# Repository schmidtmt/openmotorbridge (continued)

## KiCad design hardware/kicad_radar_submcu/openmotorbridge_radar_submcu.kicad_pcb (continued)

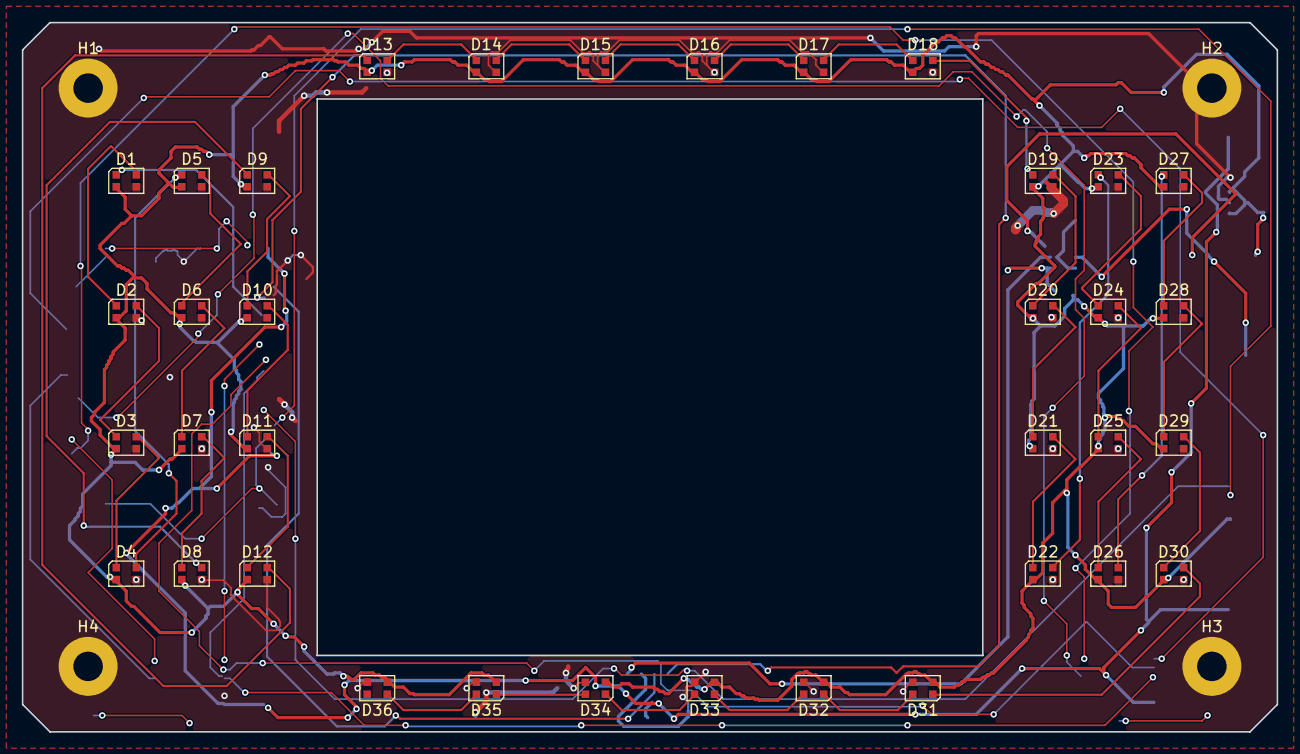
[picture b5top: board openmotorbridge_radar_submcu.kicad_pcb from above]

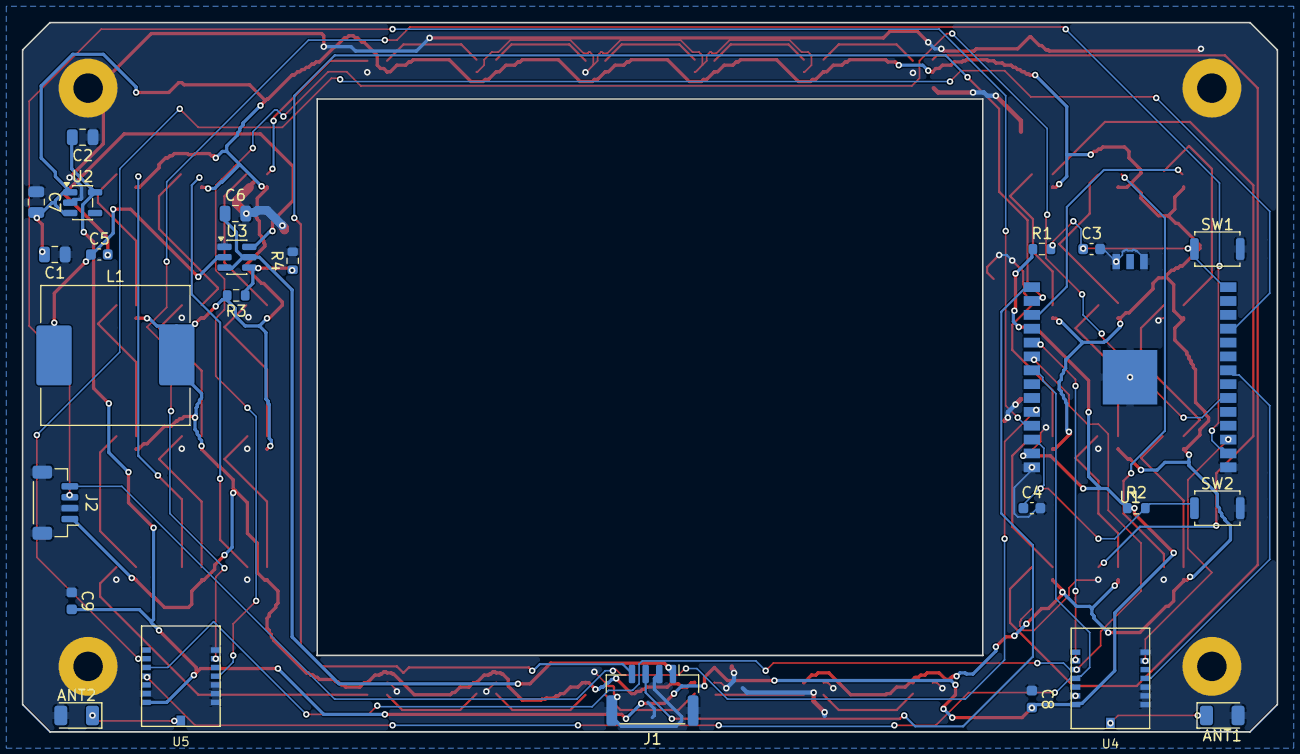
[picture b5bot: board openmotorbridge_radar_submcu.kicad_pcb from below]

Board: 2 copper layers, 115.0 x 65.0 mm, 65 parts (25 on the bottom side), 59 nets.

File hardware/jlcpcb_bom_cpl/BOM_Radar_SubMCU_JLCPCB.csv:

Designator,Comment,Footprint,LCSC Part #,Quantity
C1,10uF_16V,C_0805_2012Metric,,1
C2,10uF_10V,C_0805_2012Metric,,1
"C3, C4",100nF,C_0603_1608Metric,,2
D25,PESD5V0S2BT,SOT-23,,1
"D1, D10, D11, D12, D13, D14, D15, D16, D17, D18, D19, D2, D20, D21, D22, D23, D24, D25, D26, D27, D28, D29, D3, D30, D31, D32, D33, D34, D35, D36, D4, D5, D6, D7, D8, D9",WS2812B-2020,LED_WS2812B-2020_PLCC4_2.0x2.0mm,,36
"H1, H2, H3, H4",M2.5_MountingHole,MountingHole_2.7mm_M2.5_Pad,,4
J1,JST_SH_4P_CENTRAL,JST_SH_SM04B-SRSS-TB_1x04-1MP_P1.00mm_Horizontal,,1
J2,JST_SH_4P_MR20,JST_SH_SM04B-SRSS-TB_1x04-1MP_P1.00mm_Horizontal,,1
J3,U.FL_5G9_V2X,U.FL_Hirose_U.FL-R-SMT-1_Vertical,,1
"R1, R2",10k,R_0603_1608Metric,,2
SW1,BOOT_SW,SW_Push_SPST_NO_Alps_SKRK,,1
SW2,RESET_SW,SW_Push_SPST_NO_Alps_SKRK,,1
U1,ESP32-C5-WROOM-1U,ESP32-C3-WROOM-02U,,1
U2,TPS7A0533,SOT-23-5,,1

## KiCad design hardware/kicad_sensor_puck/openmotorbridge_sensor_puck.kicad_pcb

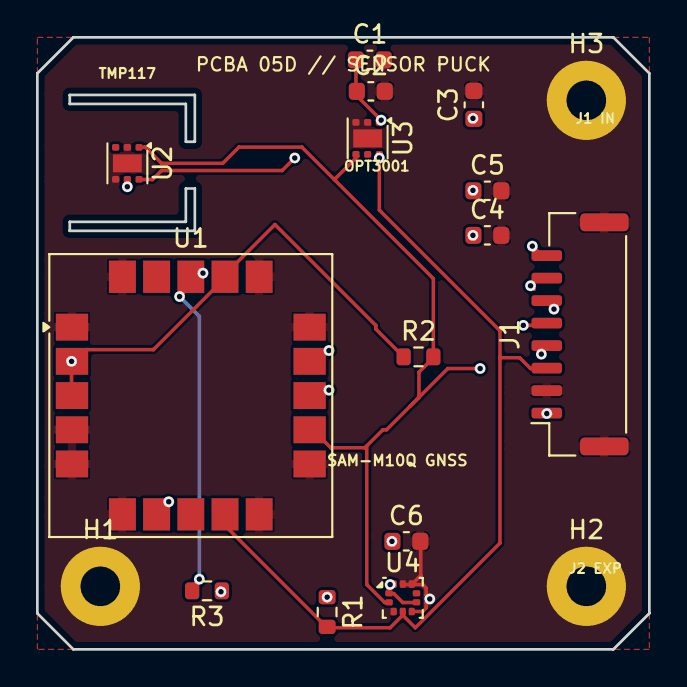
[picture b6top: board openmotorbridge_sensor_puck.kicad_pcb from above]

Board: 4 copper layers, 34.0 x 34.0 mm, 17 parts (0 on the bottom side), 8 nets.

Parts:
C1, C3, C4, C6: 0.1uF; C_0603_1608Metric
C2: 4.7uF; C_0603_1608Metric
C5: 10uF; C_0603_1608Metric
H1, H2, H3: M2; MountingHole_2.2mm_M2_Pad
J1: JST_GH_08P_SENSOR_IN; JST_GH_SM08B-GHS-TB_1x08-1MP_P1.25mm_Horizontal
R1, R2: 4.7k; R_0603_1608Metric
R3: 10k; R_0603_1608Metric
U1: SAM-M10Q; ublox_SAM-M8Q
U2: TMP117AIDRVR; WSON-6-1EP_2x2mm_P0.65mm_EP1x1.6mm
U3: OPT3001DNPR; WSON-6-1EP_2x2mm_P0.65mm_EP1x1.6mm
U4: BMP390; ST_HLGA-10_2x2mm_P0.5mm_LayoutBorder3x2y

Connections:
GND: C1.2, C2.2, C3.2, C4.2, C5.2, C6.2, H1.1 (1_1), H2.1 (1_1), H3.1 (1_1), J1.2, J1.MP, U1.1, U1.4, U1.5, U1.6, U1.10, U1.11, U1.15, U1.16, U1.20, U2.2, U2.4, U2.7, U3.2, U3.3, U3.7, U4.3, U4.5, U4.8, U4.9
GNSS_RESET_N: J1.8, R3.2, U1.18
GNSS_RXD: J1.7, U1.14
GNSS_TIMEPULSE: J1.5, U1.7
GNSS_TXD: J1.6, U1.13
I2C_SCL: J1.4, R2.2, U1.12, U2.1, U3.4, U4.2
I2C_SDA: J1.3, R1.2, U1.9, U2.6, U3.6, U4.4
VCC_3V3: C1.1, C2.1, C3.1, C4.1, C5.1, C6.1, J1.1, R1.1, R2.1, R3.1, U1.2, U1.3, U1.17, U2.5, U3.1, U4.1, U4.6, U4.10

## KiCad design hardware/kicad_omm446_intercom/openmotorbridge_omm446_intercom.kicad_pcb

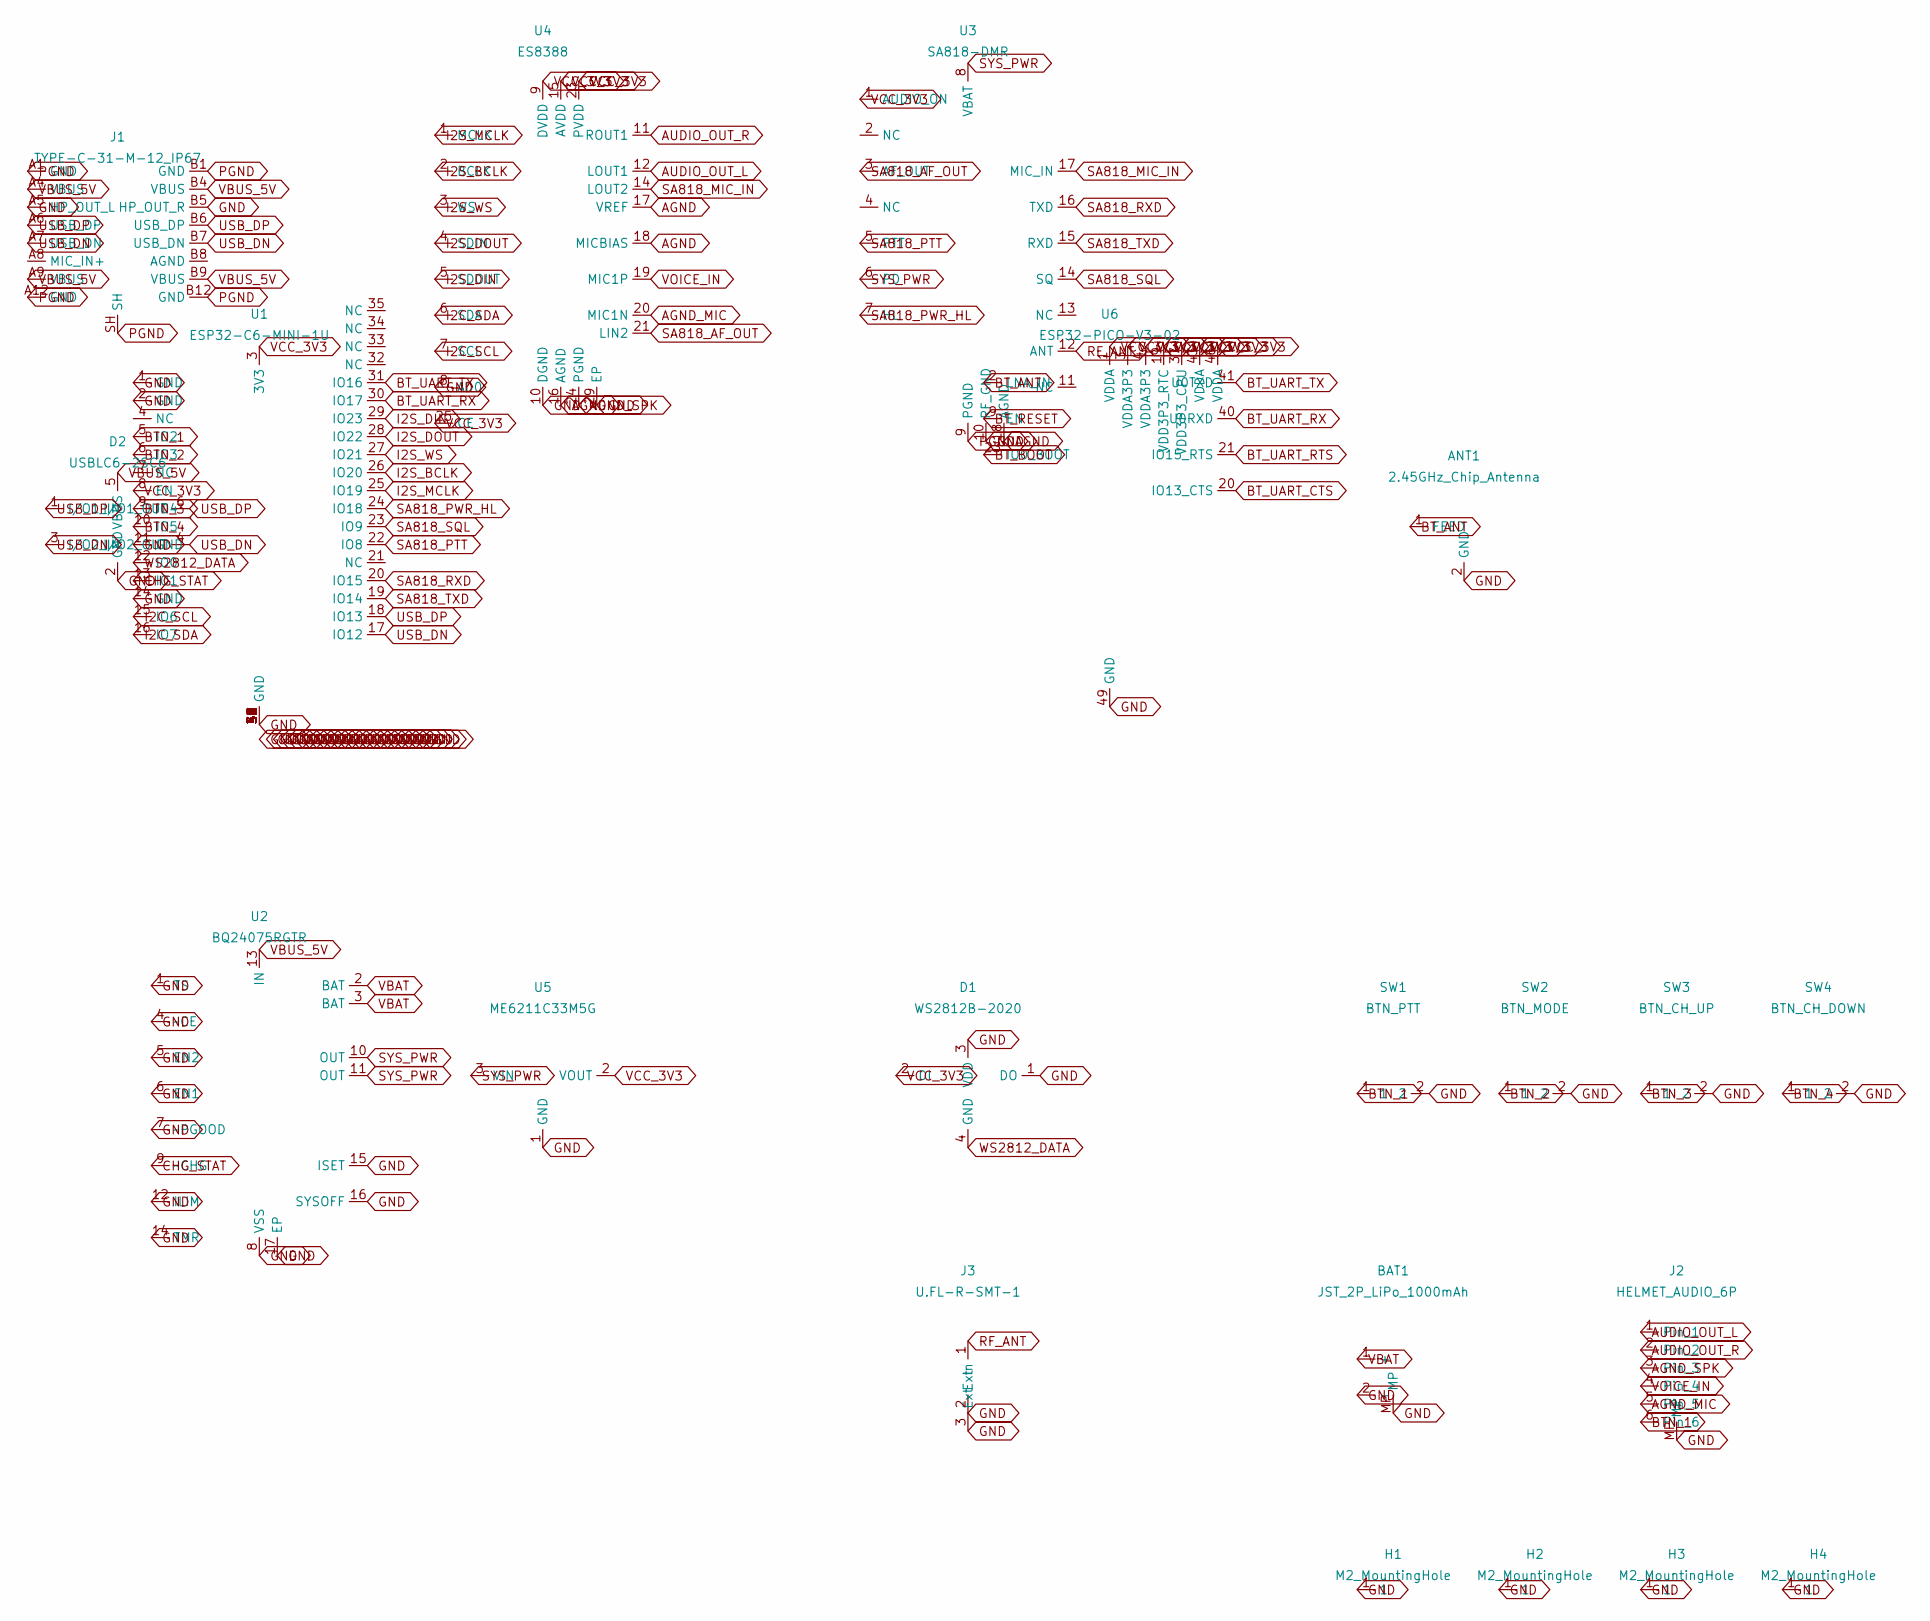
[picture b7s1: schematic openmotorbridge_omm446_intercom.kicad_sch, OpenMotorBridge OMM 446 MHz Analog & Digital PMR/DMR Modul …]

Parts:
ANT1: 2.45GHz_Chip_Antenna; Johanson_2450AT18x100; LCSC C2909988
BAT1: JST_2P_LiPo_1000mAh; JST_SH_BM02B-SRSS-TB_1x02-1MP_P1.00mm_Vertical
D1: WS2812B-2020; LED_WS2812B-2020_PLCC4_2.0x2.0mm
D2: USBLC6-2SC6; SOT-23-6
H1, H2, H3, H4: M2_MountingHole; MountingHole_2.2mm_M2_Pad
J1: TYPE-C-31-M-12_IP67; USB_C_Receptacle_HRO_TYPE-C-31-M-12
J2: HELMET_AUDIO_6P; JST_SH_BM06B-SRSS-TB_1x06-1MP_P1.00mm_Vertical
J3: U.FL-R-SMT-1; U.FL_Hirose_U.FL-R-SMT-1_Vertical
SW1: BTN_PTT; SW_Push_SPST_NO_Alps_SKRK
SW2: BTN_MODE; SW_Push_SPST_NO_Alps_SKRK
SW3: BTN_CH_UP; SW_Push_SPST_NO_Alps_SKRK
SW4: BTN_CH_DOWN; SW_Push_SPST_NO_Alps_SKRK
U1: ESP32-C6-MINI-1U
U2: BQ24075RGTR; VQFN-16-1EP_3x3mm_P0.5mm_EP1.8x1.8mm
U3: SA818-DMR; NiceRF_SA818-DMR_SMD_38x16mm
U4: ES8388; QFN-28-1EP_4x4mm_P0.4mm_EP2.4x2.4mm
U5: ME6211C33M5G; SOT-23
U6: ESP32-PICO-V3-02; QFN-48-1EP_7x7mm_P0.5mm_EP5.3x5.3mm; LCSC C2686884

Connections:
AGND: U3.18 (AGND), U4.16 (AGND), U4.17 (VREF), U4.18 (MICBIAS)
AGND_MIC: J2.5, U4.20 (MIC1N)
AGND_SPK: J2.3, U4.24 (PGND)
AUDIO_OUT_L: J2.1, U4.12 (LOUT1)
AUDIO_OUT_R: J2.2, U4.11 (ROUT1)
BTN_1: J2.6, SW1.1, U1.5 (IO2)
BTN_2: SW2.1, U1.6 (IO3)
BTN_3: SW3.1, U1.9 (IO4)
BTN_4: SW4.1, U1.10 (IO5)
BT_ANT: ANT1.1 (FEED), U6.2 (LNA_IN)
BT_BOOT: U6.23 (IO0_BOOT)
BT_RESET: U6.9 (EN)
BT_UART_CTS: U6.20 (IO13_CTS)
BT_UART_RTS: U6.21 (IO15_RTS)
BT_UART_RX: U1.30 (IO17), U6.40 (U0RXD)
BT_UART_TX: U1.31 (IO16), U6.41 (U0TXD)
CHG_STAT: U1.13 (IO1), U2.9 (~CHG)
GND: ANT1.2 (GND), BAT1.2 (-), BAT1.MP, D1.1 (DO), D1.3 (VDD), D2.2 (GND), H1.1 (1_1), H2.1 (1_1), H3.1 (1_1), H4.1 (1_1), J1.A5 (HP_OUT_L), J1.B5 (HP_OUT_R), J2.MP, J3.2 (Ext), J3.3 (Ext), SW1.2, SW2.2, SW3.2, SW4.2, U1.1 (GND), U1.2 (GND), U1.11 (GND), U1.14 (GND), U1.36 (GND), U1.37 (GND), U1.38 (GND), U1.39 (GND), U1.40 (GND), U1.41 (GND), U1.42 (GND), U1.43 (GND), U1.44 (GND), U1.45 (GND), U1.46 (GND), U1.47 (GND), U1.48 (GND), U1.49 (GND), U1.50 (GND), U1.51 (GND), U1.52 (GND), U1.53 (GND), U2.1 (TS), U2.4 (~CE), U2.5 (EN2), U2.6 (EN1), U2.7 (~PGOOD), U2.8 (VSS), U2.12 (ILIM), U2.14 (TMR), U2.15 (ISET), U2.16 (SYSOFF), U2.17 (EP), U3.10 (RF_GND), U4.8 (AD0), U4.10 (DGND), U4.29 (EP), U5.1 (GND), U6.49 (GND)
I2C_SCL: U1.15 (IO6), U4.7 (SCL)
I2C_SDA: U1.16 (IO7), U4.6 (SDA)
I2S_BCLK: U1.26 (IO20), U4.2 (BCLK)
I2S_DIN: U1.29 (IO23), U4.5 (SDOUT)
I2S_DOUT: U1.28 (IO22), U4.4 (SDIN)
I2S_MCLK: U1.25 (IO19), U4.1 (MCLK)
I2S_WS: U1.27 (IO21), U4.3 (WS)
PGND: J1.A1 (GND), J1.A12 (GND), J1.B1 (GND), J1.B12 (GND), J1.SH, U3.9 (PGND)
RF_ANT: J3.1 (In), U3.12 (ANT)
SA818_AF_OUT: U3.3 (AF_OUT), U4.21 (LIN2)
SA818_MIC_IN: U3.17 (MIC_IN), U4.14 (LOUT2)
SA818_PTT: U1.22 (IO8), U3.5 (PTT)
SA818_PWR_HL: U1.24 (IO18), U3.7 (HL)
SA818_RXD: U1.20 (IO15), U3.16 (TXD)
SA818_SQL: U1.23 (IO9), U3.14 (SQ)
SA818_TXD: U1.19 (IO14), U3.15 (RXD)
SYS_PWR: U2.10 (OUT), U2.11 (OUT), U3.6 (PD), U3.8 (VBAT), U5.3 (VIN)
USB_DN: D2.3 (I/O2_IN), D2.4 (I/O2_OUT), J1.A7 (USB_DN), J1.B7 (USB_DN), U1.17 (IO12)
USB_DP: D2.1 (I/O1_IN), D2.6 (I/O1_OUT), J1.A6 (USB_DP), J1.B6 (USB_DP), U1.18 (IO13)
VBAT: BAT1.1 (+), U2.2 (BAT), U2.3 (BAT)
VBUS_5V: D2.5 (VBUS), J1.A4 (VBUS), J1.A9 (VBUS), J1.B4 (VBUS), J1.B9 (VBUS), U2.13 (IN)
VCC_3V3: D1.2 (DI), U1.3 (3V3), U1.8 (EN), U3.1 (AUDIO_ON), U4.9 (DVDD), U4.15 (AVDD), U4.23 (PVDD), U4.25 (CE), U5.2 (VOUT), U6.1 (VDDA), U6.3 (VDDA3P3), U6.4 (VDDA3P3), U6.19 (VDD3P3_RTC), U6.37 (VDD3P3_CPU), U6.43 (VDDA), U6.46 (VDDA)
VOICE_IN: J2.4, U4.19 (MIC1P)
WS2812_DATA: D1.4 (GND), U1.12 (IO0)

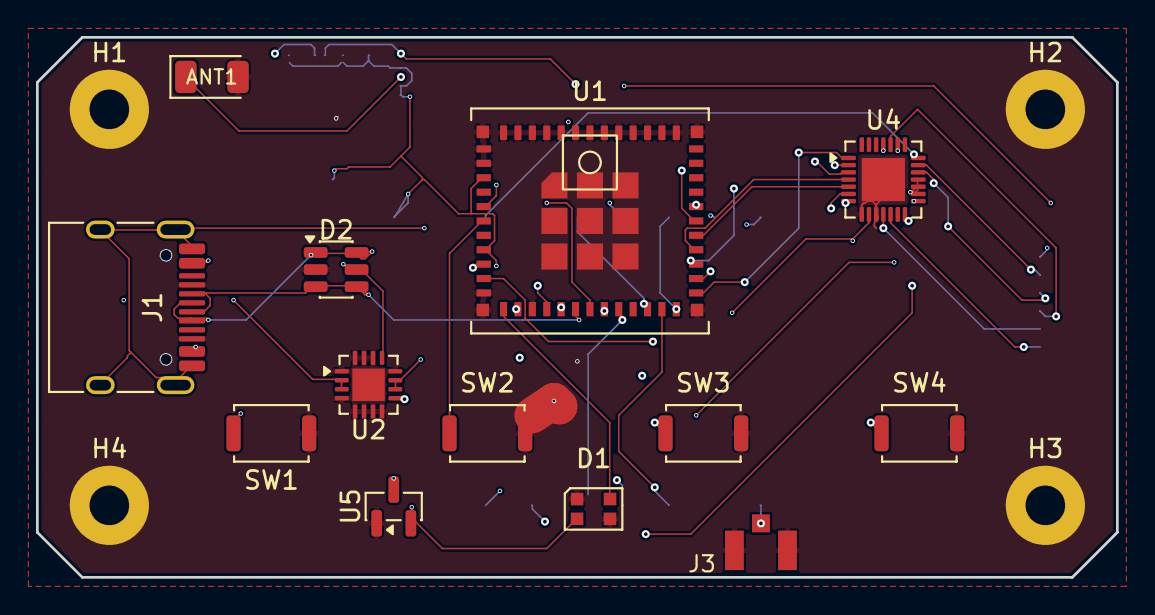
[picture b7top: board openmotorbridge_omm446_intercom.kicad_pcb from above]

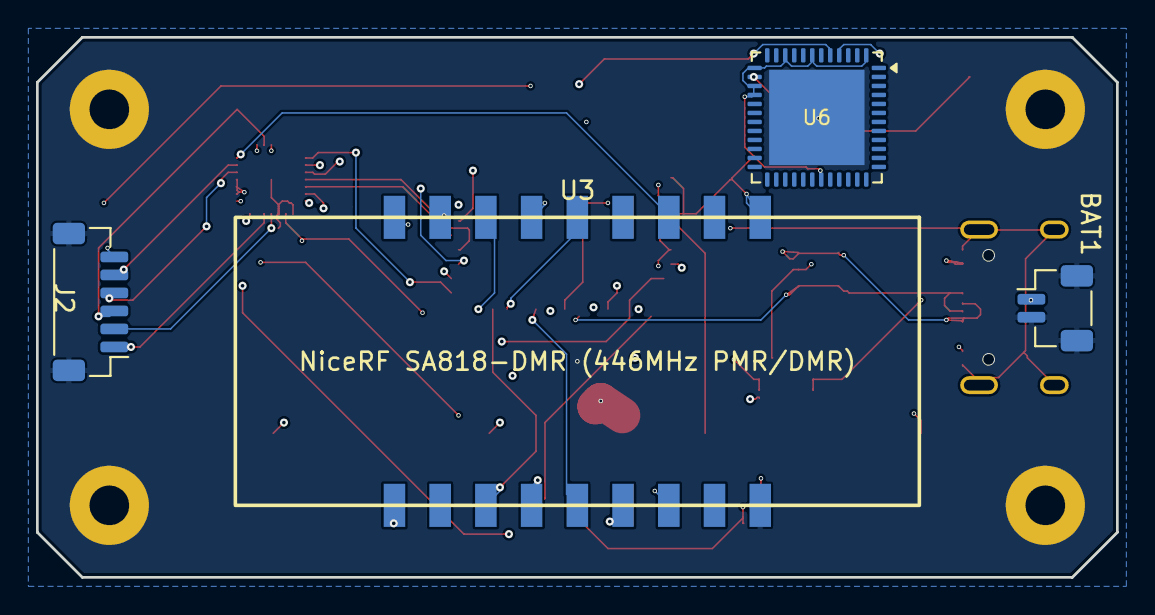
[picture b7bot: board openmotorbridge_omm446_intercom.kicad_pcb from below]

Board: 4 copper layers, 60.0 x 30.0 mm, 21 parts (4 on the bottom side), 38 nets.

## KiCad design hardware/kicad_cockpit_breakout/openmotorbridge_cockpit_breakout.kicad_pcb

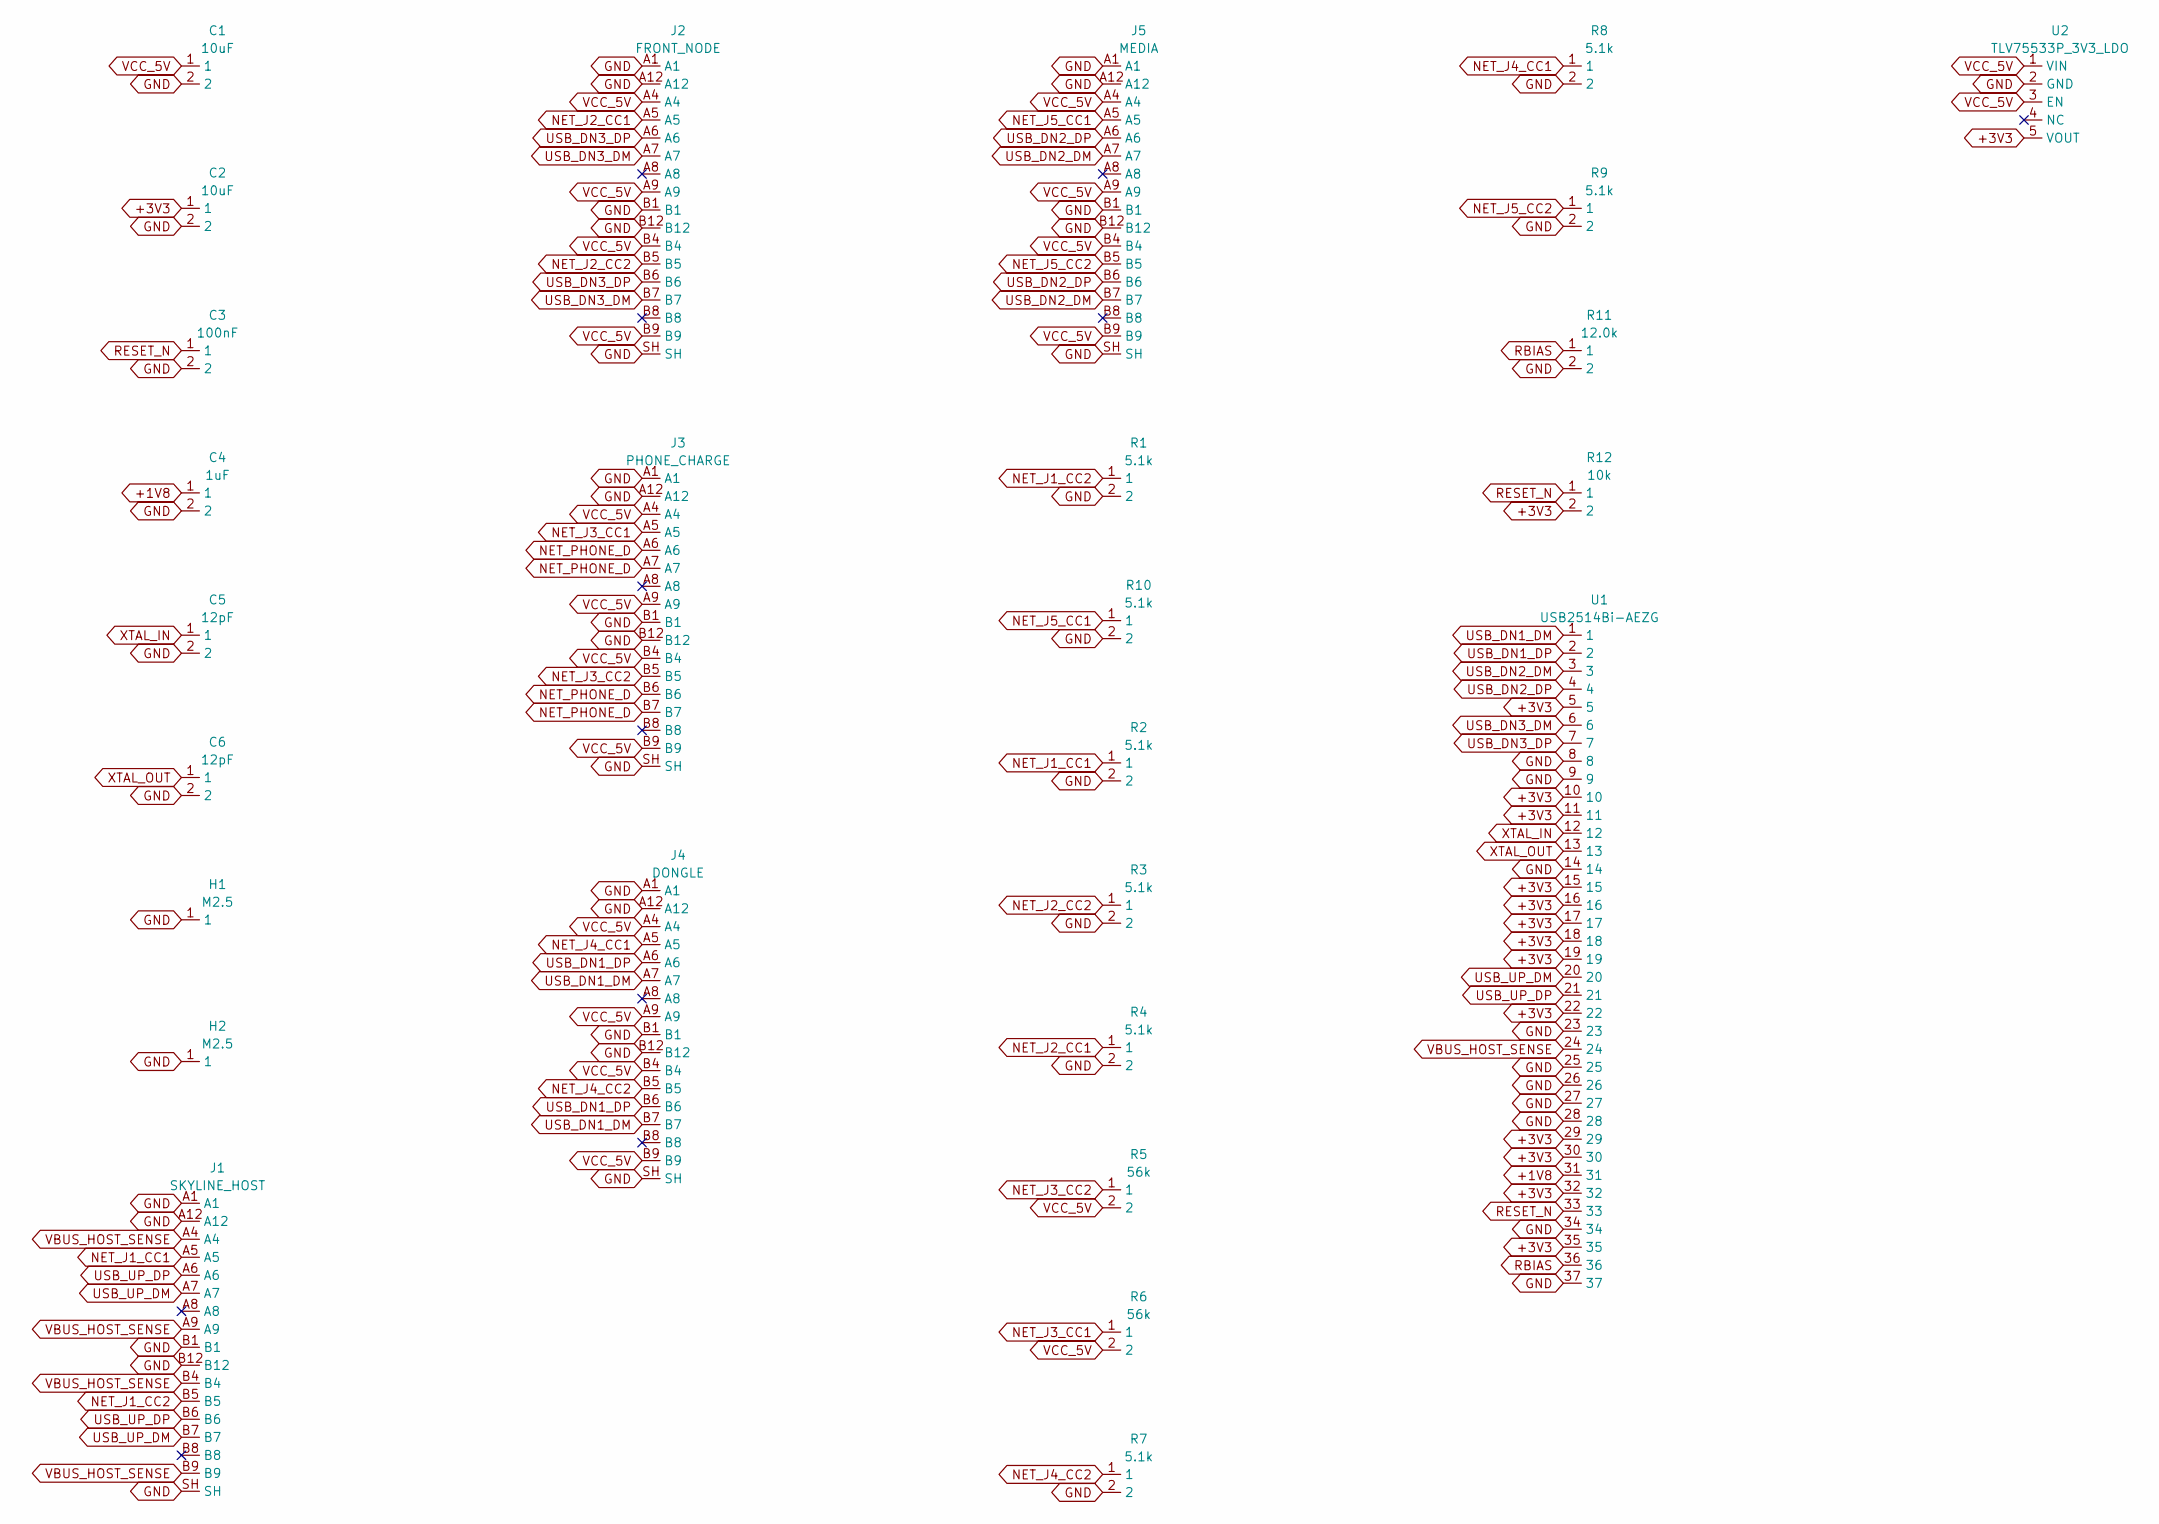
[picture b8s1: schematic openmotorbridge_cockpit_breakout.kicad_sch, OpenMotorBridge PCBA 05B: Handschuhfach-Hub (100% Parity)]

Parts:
C1, C2: 10uF; C_0603_1608Metric
C3: 100nF; C_0603_1608Metric
C4: 1uF; C_0603_1608Metric
C5, C6: 12pF; C_0603_1608Metric
H1, H2: M2.5; MountingHole_2.7mm_M2.5_Pad
J1: SKYLINE_HOST; USB_C_Receptacle_HRO_TYPE-C-31-M-12
J2: FRONT_NODE; USB_C_Receptacle_HRO_TYPE-C-31-M-12
J3: PHONE_CHARGE; USB_C_Receptacle_HRO_TYPE-C-31-M-12
J4: DONGLE; USB_C_Receptacle_HRO_TYPE-C-31-M-12
J5: MEDIA; USB_C_Receptacle_HRO_TYPE-C-31-M-12
R1, R2, R3, R4, R7, R8, R9, R10: 5.1k; R_0603_1608Metric
R5, R6: 56k; R_0603_1608Metric
R11: 12.0k; R_0603_1608Metric
R12: 10k; R_0603_1608Metric
U1: USB2514Bi-AEZG; QFN-36-1EP_6x6mm_P0.5mm_EP4.1x4.1mm
U2: TLV75533P_3V3_LDO; SOT-23-5

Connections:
+1V8: C4.1, U1.31
+3V3: C2.1, R12.2, U1.5, U1.10, U1.11, U1.15, U1.16, U1.17, U1.18, U1.19, U1.22, U1.29, U1.30, U1.32, U1.35, U2.5 (VOUT)
GND: C1.2, C2.2, C3.2, C4.2, C5.2, C6.2, H1.1 (1_1), H2.1 (1_1), J1.A1, J1.A12, J1.B1, J1.B12, J1.SH, J2.A1, J2.A12, J2.B1, J2.B12, J2.SH, J3.A1, J3.A12, J3.B1, J3.B12, J3.SH, J4.A1, J4.A12, J4.B1, J4.B12, J4.SH, J5.A1, J5.A12, J5.B1, J5.B12, J5.SH, R1.2, R2.2, R3.2, R4.2, R7.2, R8.2, R9.2, R10.2, R11.2, U1.8, U1.9, U1.14, U1.23, U1.25, U1.26, U1.27, U1.28, U1.34, U1.37, U2.2 (GND)
NET_J1_CC1: J1.A5, R2.1
NET_J1_CC2: J1.B5, R1.1
NET_J2_CC1: J2.A5, R4.1
NET_J2_CC2: J2.B5, R3.1
NET_J3_CC1: J3.A5, R6.1
NET_J3_CC2: J3.B5, R5.1
NET_J4_CC1: J4.A5, R8.1
NET_J4_CC2: J4.B5, R7.1
NET_J5_CC1: J5.A5, R10.1
NET_J5_CC2: J5.B5, R9.1
NET_PHONE_D: J3.A6, J3.A7, J3.B6, J3.B7
RBIAS: R11.1, U1.36
RESET_N: C3.1, R12.1, U1.33
USB_DN1_DM: J4.A7, J4.B7, U1.1
USB_DN1_DP: J4.A6, J4.B6, U1.2
USB_DN2_DM: J5.A7, J5.B7, U1.3
USB_DN2_DP: J5.A6, J5.B6, U1.4
USB_DN3_DM: J2.A7, J2.B7, U1.6
USB_DN3_DP: J2.A6, J2.B6, U1.7
USB_UP_DM: J1.A7, J1.B7, U1.20
USB_UP_DP: J1.A6, J1.B6, U1.21
VBUS_HOST_SENSE: J1.A4, J1.A9, J1.B4, J1.B9, U1.24
VCC_5V: C1.1, J2.A4, J2.A9, J2.B4, J2.B9, J3.A4, J3.A9, J3.B4, J3.B9, J4.A4, J4.A9, J4.B4, J4.B9, J5.A4, J5.A9, J5.B4, J5.B9, R5.2, R6.2, U2.1 (VIN), U2.3 (EN)
XTAL_IN: C5.1, U1.12
XTAL_OUT: C6.1, U1.13

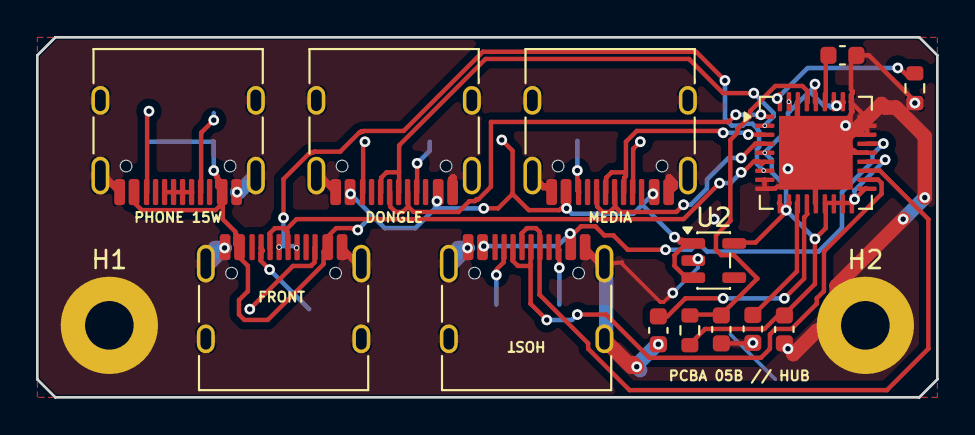
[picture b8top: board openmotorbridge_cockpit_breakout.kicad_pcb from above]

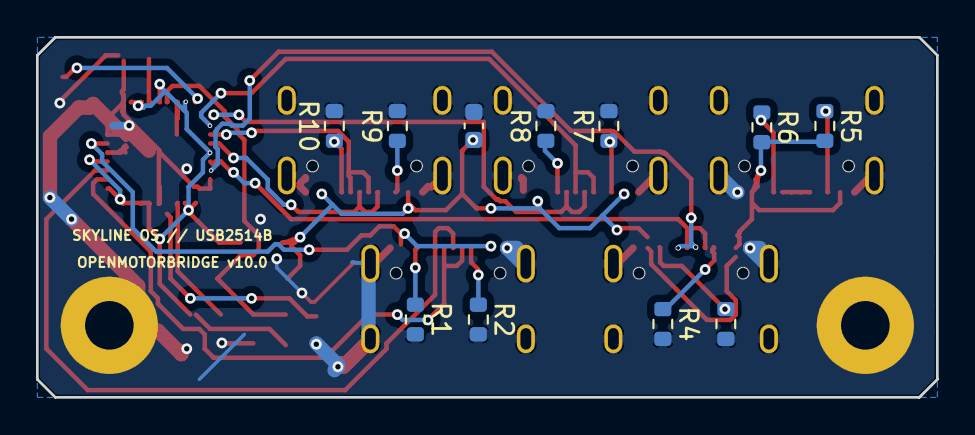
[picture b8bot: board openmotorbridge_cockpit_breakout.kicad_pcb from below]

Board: 2 copper layers, 50.0 x 20.0 mm, 27 parts (11 on the bottom side), 28 nets.
